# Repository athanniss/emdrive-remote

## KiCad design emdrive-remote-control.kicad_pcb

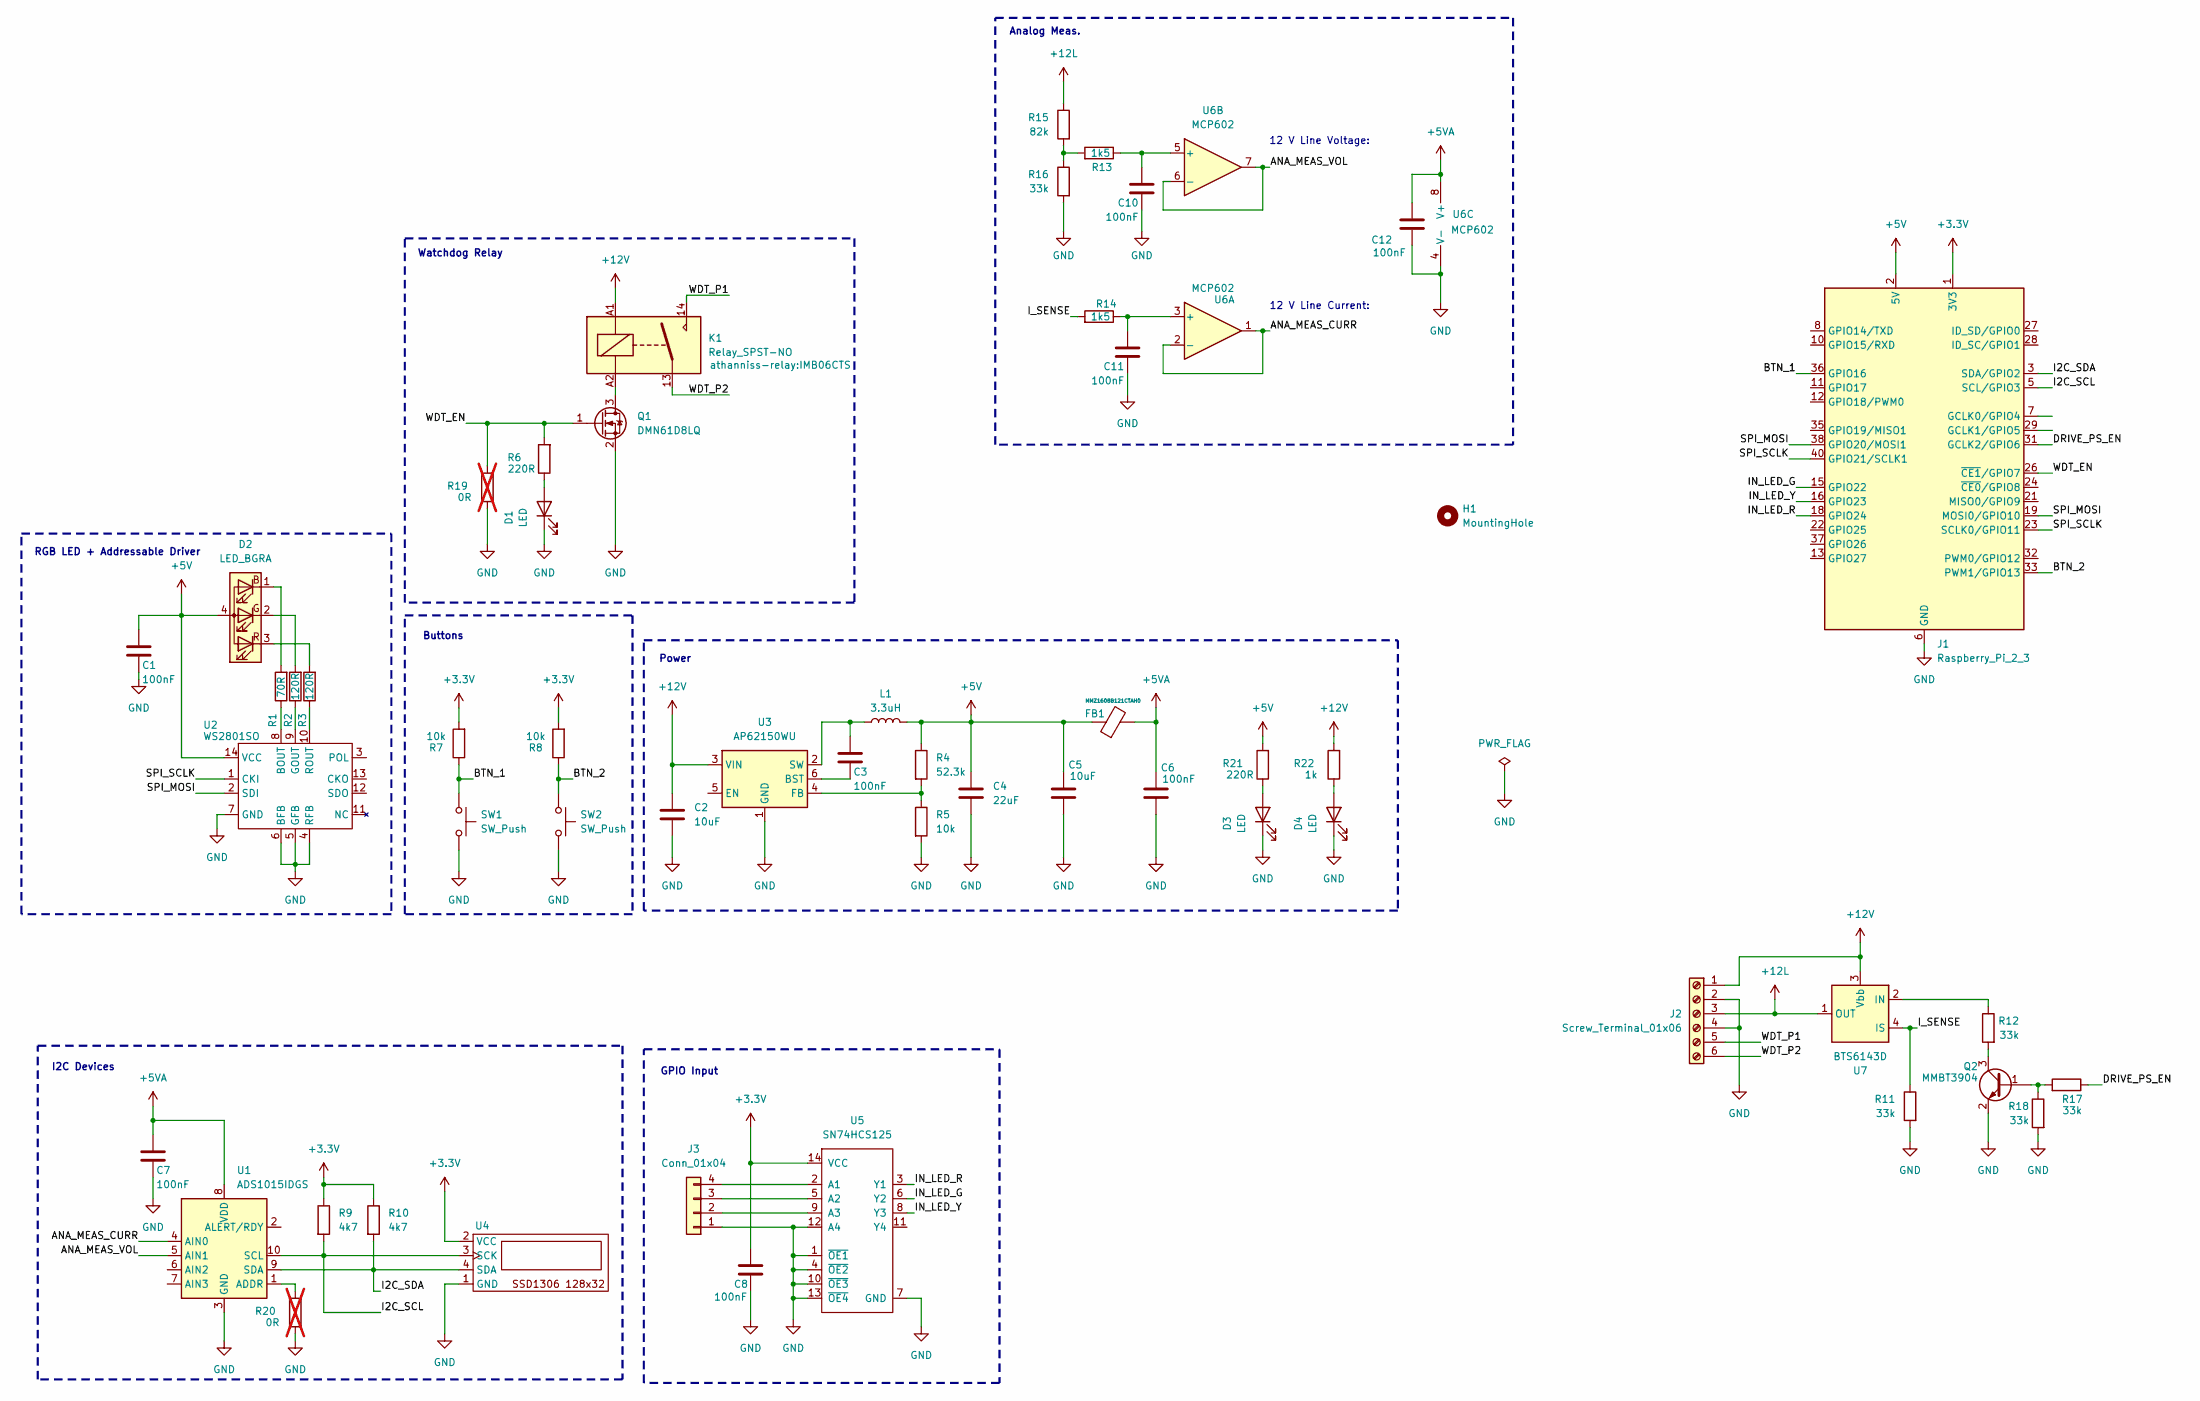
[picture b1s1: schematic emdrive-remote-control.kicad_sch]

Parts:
C1, C3, C6, C7, C8, C10, C11, C12: 100nF; C_0603_1608Metric_Pad1.08x0.95mm_HandSolder; Manufacturer P/N CL10B104KB8NNNC; Digikey P/N 1276-1000-1-ND
C2, C5: 10uF; C_0805_2012Metric_Pad1.18x1.45mm_HandSolder; Manufacturer P/N GRM21BR61H106ME43L; Digikey P/N 490-18664-1-ND
C4: 22uF; C_1210_3225Metric_Pad1.33x2.70mm_HandSolder
D1, D3, D4: LED; LED_0805_2012Metric
D2: LED_BGRA; LED_BL-FL7680RGB
FB1: MMZ1608B121CTAH0; L_0603_1608Metric_Pad1.05x0.95mm_HandSolder; Manufacturer P/N MMZ1608B121CTAH0; Digikey P/N 445-2164-1-ND
H1: MountingHole; MountingHole_3.2mm_M3_DIN965
J1: Raspberry_Pi_2_3; Raspberry_Pi_Zero_Socketed_THT_FaceDown_MountingHoles_Dupon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
J2: Screw_Terminal_01x06; Terminal_Block_SERIES 4115_5.08_Spring_6POS
J3: Conn_01x04; JST_XH_S4B-XH-A_1x04_P2.50mm_Horizontal
K1: Relay_SPST-NO; IMB06CTS; Manufacturer P/N 1462041-6; Digikey P/N PB1248-ND
L1: 3.3uH; L_Wuerth_WE-LHMI-Typ; Manufacturer P/N 74437336033; Digikey P/N 732-6166-1-ND
Q1: DMN61D8LQ; SOT-23; Manufacturer P/N DMN61D8LQ-13; Digikey P/N DMN61D8LQ-13DICT-ND
Q2: MMBT3904; SOT-23
R1: 70R; R_0603_1608Metric_Pad0.98x0.95mm_HandSolder
R2, R3: 120R; R_0603_1608Metric_Pad0.98x0.95mm_HandSolder
R4: 52.3k; R_0603_1608Metric_Pad0.98x0.95mm_HandSolder
R5, R7, R8: 10k; R_0603_1608Metric_Pad0.98x0.95mm_HandSolder
R6, R21: 220R; R_0603_1608Metric_Pad0.98x0.95mm_HandSolder
R9, R10: 4k7; R_0603_1608Metric_Pad0.98x0.95mm_HandSolder
R11, R12, R16, R17, R18: 33k; R_0603_1608Metric_Pad0.98x0.95mm_HandSolder
R13, R14: 1k5; R_0603_1608Metric_Pad0.98x0.95mm_HandSolder
R15: 82k; R_0603_1608Metric_Pad0.98x0.95mm_HandSolder
R19, R20: 0R; R_0603_1608Metric_Pad0.98x0.95mm_HandSolder; not fitted
R22: 1k; R_0603_1608Metric_Pad0.98x0.95mm_HandSolder
SW1, SW2: SW_Push; SW_PUSH_6mm_H8mm; Manufacturer P/N TS02-66-80-BK-100-SCR-D; Digikey P/N 2223-TS02-66-80-BK-100-SCR-D-ND
U1: ADS1015IDGS; TSSOP-10_3x3mm_P0.5mm; Manufacturer P/N ADS1015IDGSR; Digikey P/N 296-41185-1-ND
U2: WS2801SO; SO-14_3.9x8.65mm_P1.27mm
U3: AP62150WU; TSOT-23-6; Manufacturer P/N AP62150WU-7; Digikey P/N 31-AP62150WU-7CT-ND
U4: SSD1306-0.91-OLED-4pin-128x32
U5: SN74HCS125; SOIC-14_3.9x8.7mm_P1.27mm; Manufacturer P/N SN74HCS125DR; Digikey P/N 296-SN74HCS125DRCT-ND
U6: MCP602; SOIC-8_3.9x4.9mm_P1.27mm; Manufacturer P/N MCP602T-I/SN; Digikey P/N MCP602T-I/SNCT-ND
U7: BTS6143D; TO-252-4

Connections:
+3.3V: C8.2, J1.1 (3V3), J1.17 (3V3), R7.2, R8.2, R9.1, R10.1, U4.2 (VCC), U5.14 (VCC)
+5V: C1.2, C4.2, C5.2, D2.4 (A), FB1.1, J1.2 (5V), J1.4 (5V), L1.2, R4.1, R21.2, U2.14 (VCC)
+5VA: C6.2, C7.2, C12.2, FB1.2, U1.8 (VDD), U6.8 (V+)
+12L: J2.3, R15.1, U7.1 (OUT), U7.5 (OUT)
+12V: C2.2, J2.1, K1.A1, R22.2, U3.3 (VIN), U7.3 (Vbb)
/ANA_MEAS_CURR: U1.4 (AIN0), U6.1, U6.2 (-)
/ANA_MEAS_VOL: U1.5 (AIN1), U6.6 (-), U6.7
/BTN_1: J1.36 (GPIO16), R7.1, SW1.1
/BTN_2: J1.33 (PWM1/GPIO13), R8.1, SW2.1
/DRIVE_PS_EN: J1.31 (GCLK2/GPIO6), R17.1
/I2C_SCL: J1.5 (SCL/GPIO3), R9.2, U1.10 (SCL), U4.3 (SCK)
/I2C_SDA: J1.3 (SDA/GPIO2), R10.2, U1.9 (SDA), U4.4 (SDA)
/IN_LED_G: J1.15 (GPIO22), U5.6 (Y2)
/IN_LED_R: J1.18 (GPIO24), U5.3 (Y1)
/IN_LED_Y: J1.16 (GPIO23), U5.8 (Y3)
/I_SENSE: R11.1, R14.2, U7.4 (IS)
/SPI_MOSI: J1.19 (MOSI0/GPIO10), J1.38 (GPIO20/MOSI1), U2.2 (SDI)
/SPI_SCLK: J1.23 (SCLK0/GPIO11), J1.40 (GPIO21/SCLK1), U2.1 (CKI)
/WDT_EN: J1.26 (~CE1/GPIO7), Q1.1 (G), R6.2, R19.2
/WDT_P1: J2.5, K1.14
/WDT_P2: J2.6, K1.13
GND: C1.1, C2.1, C4.1, C5.1, C6.1, C7.1, C8.1, C10.1, C11.1, C12.1, D1.1 (K), D3.1 (K), D4.1 (K), J1.6 (GND), J1.9 (GND), J1.14 (GND), J1.20 (GND), J1.25 (GND), J1.30 (GND), J1.34 (GND), J1.39 (GND), J2.2, J2.4, J3.1, Q1.2 (S), Q2.2 (E), R5.2, R11.2, R16.2, R18.2, R19.1, R20.1, SW1.2, SW2.2, U1.3 (GND), U2.4 (RFB), U2.5 (GFB), U2.6 (BFB), U2.7 (GND), U3.1 (GND), U4.1 (GND), U5.1 (~OE1), U5.4 (~OE2), U5.7 (GND), U5.10 (~OE3), U5.12 (A4), U5.13 (~OE4), U6.4 (V-)
unnamed: D1.2 (A), R6.1
unnamed: D2.1 (BK), R1.2
unnamed: D2.2 (GK), R2.2
unnamed: D2.3 (RK), R3.2
unnamed: D3.2 (A), R21.1
unnamed: D4.2 (A), R22.1
unnamed: J3.2, U5.9 (A3)
unnamed: J3.3, U5.5 (A2)
unnamed: J3.4, U5.2 (A1)
unnamed: K1.A2, Q1.3 (D)
unnamed: Q2.1 (B), R17.2, R18.1
unnamed: Q2.3 (C), R12.2
unnamed: R13.2, R15.2, R16.1
unnamed: R20.2, U1.1 (ADDR)
unnamed: R1.1, U2.8 (BOUT)
unnamed: R2.1, U2.9 (GOUT)
unnamed: R3.1, U2.10 (ROUT)
unnamed: C3.1, U3.6 (BST)
unnamed: R4.2, R5.1, U3.4 (FB)
unnamed: C3.2, L1.1, U3.2 (SW)
unnamed: C11.2, R14.1, U6.3 (+)
unnamed: C10.2, R13.1, U6.5 (+)
unnamed: R12.1, U7.2 (IN)

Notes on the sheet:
Analog Meas.
Watchdog Relay
12 V Line Voltage:
12 V Line Current:
Buttons
I2C Devices
Power
RGB LED + Addressable Driver
GPIO Input

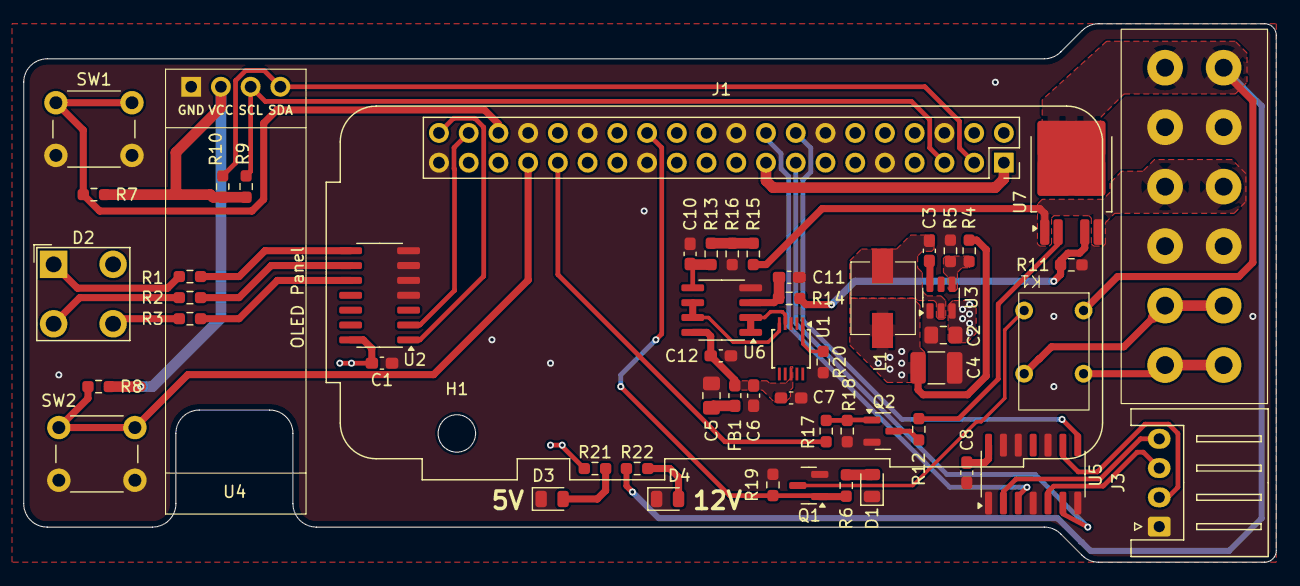
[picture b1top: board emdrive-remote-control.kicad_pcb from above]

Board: 4 copper layers, 107.0 x 46.0 mm, 55 parts (0 on the bottom side), 45 nets.

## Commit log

2024-05-14 Continues SCH, placed components on PCB
2024-05-15 Initial Routing. Minor modifications to .sch. SCH verified.
2024-05-16 Moved around modules on the PCB. Minor fixes in SCH.
